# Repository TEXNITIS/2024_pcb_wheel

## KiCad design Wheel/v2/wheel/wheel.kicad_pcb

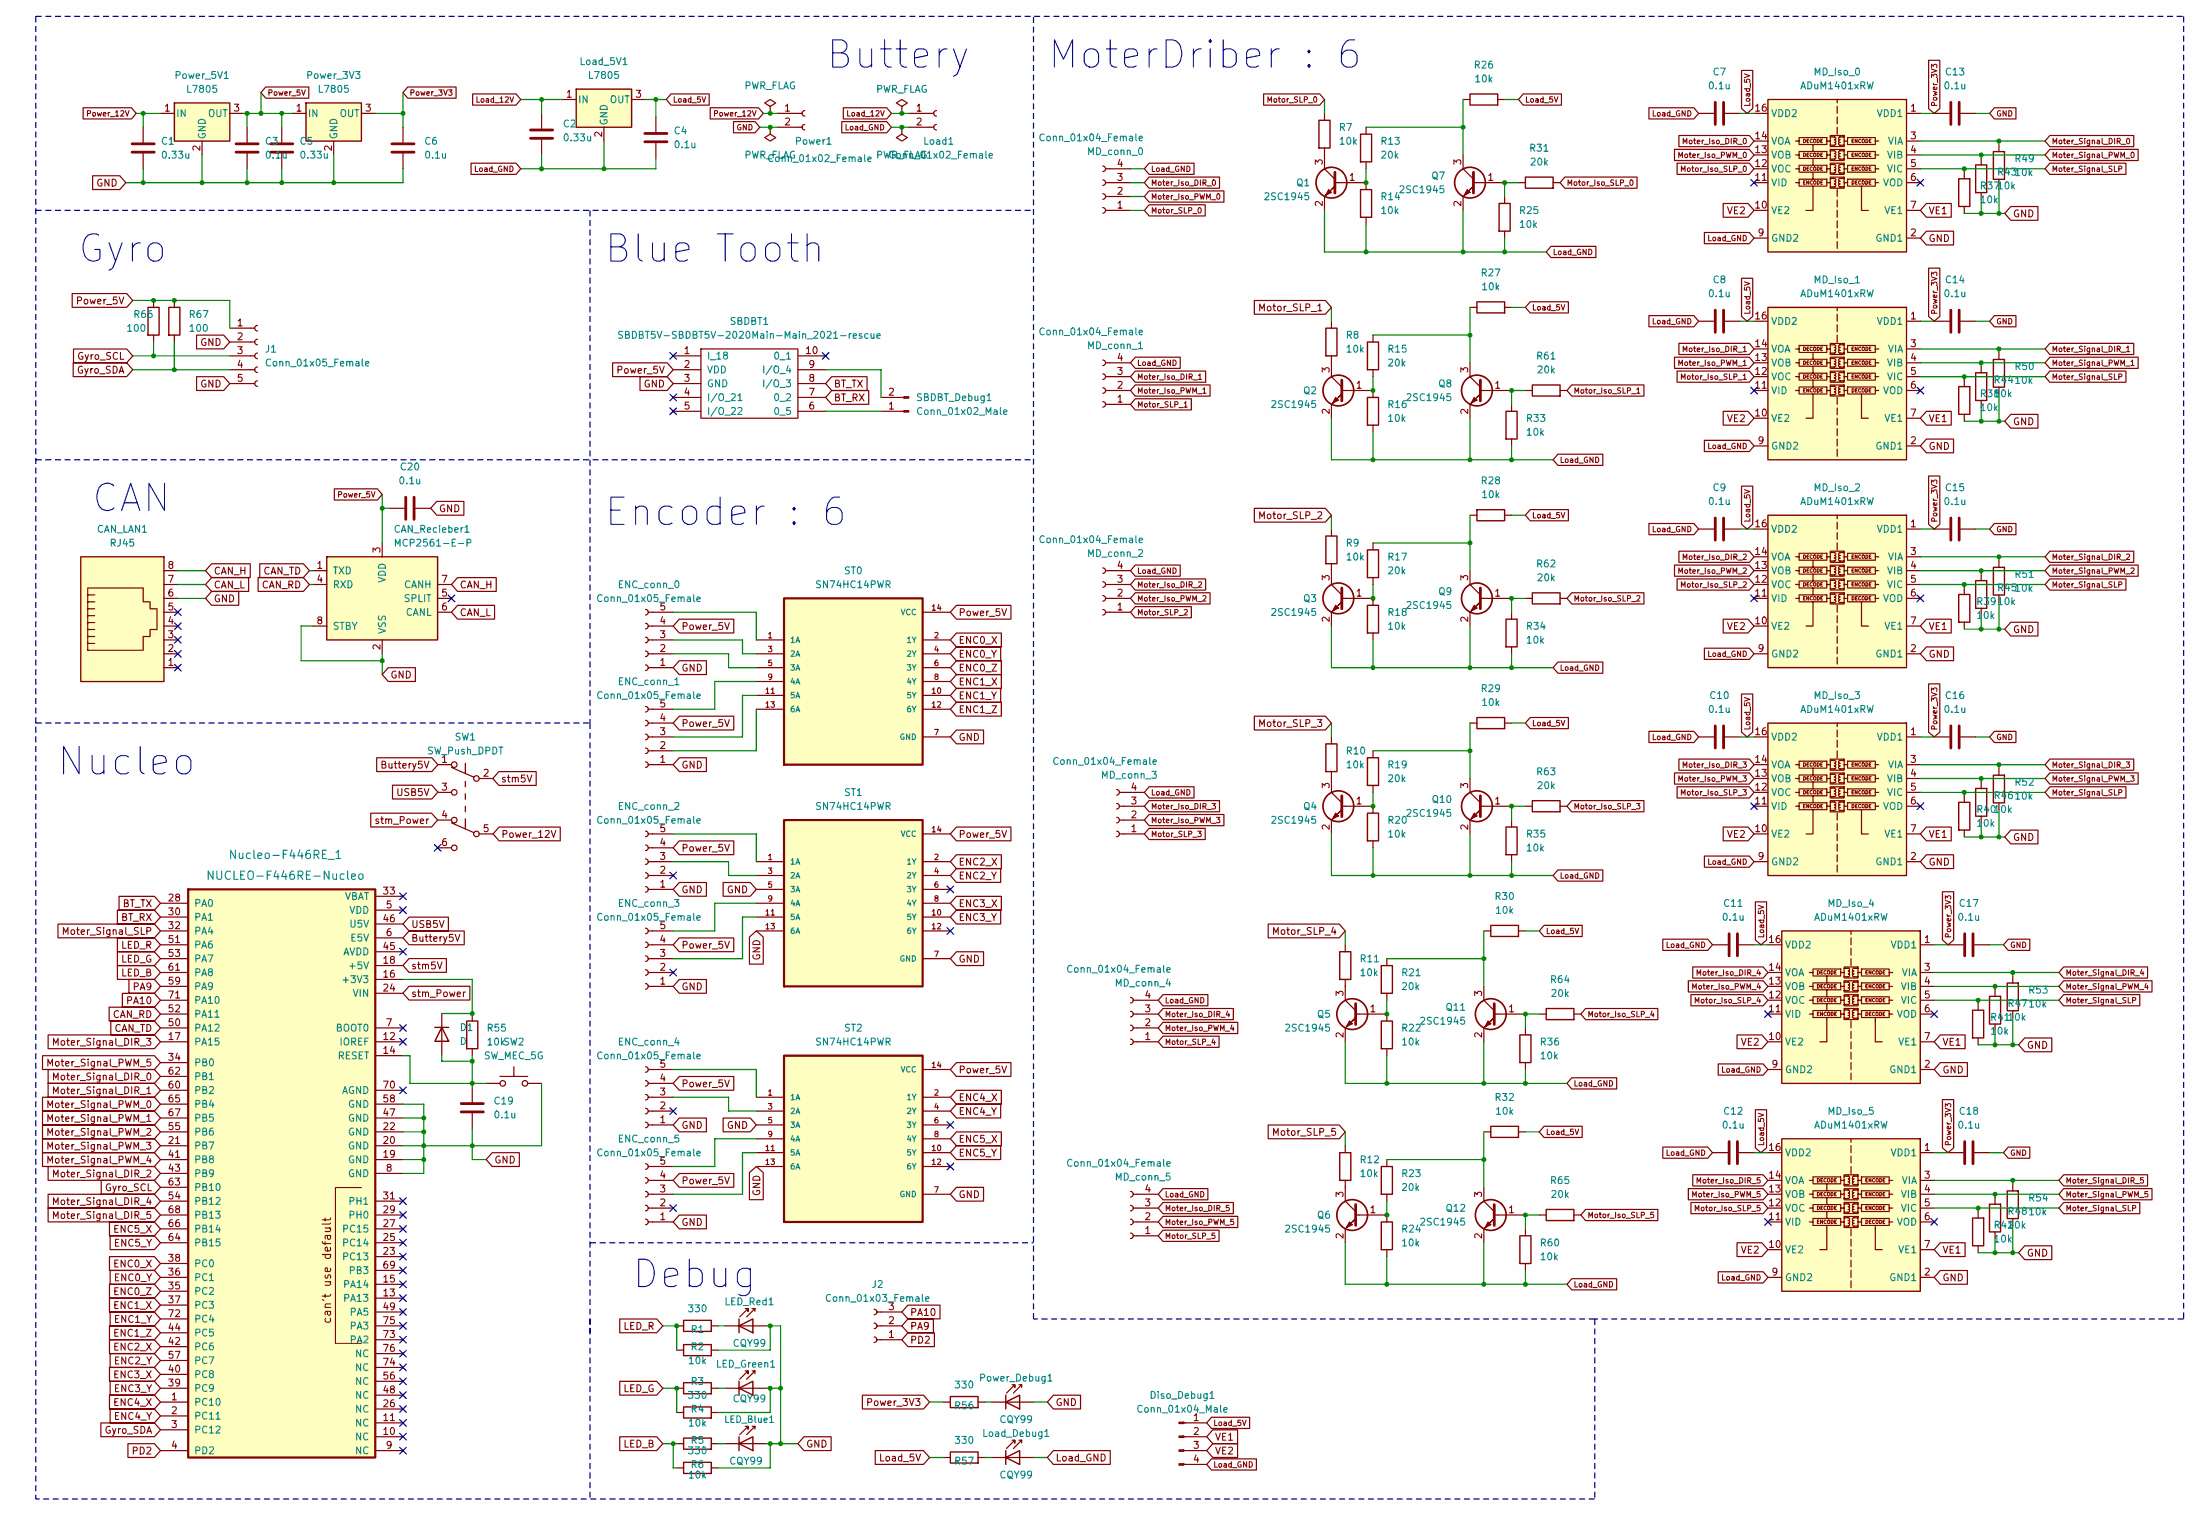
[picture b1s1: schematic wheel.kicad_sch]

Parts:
C1, C2, C5: 0.33u; C_0603_1608Metric_Pad1.08x0.95mm_HandSolder; LCSC C5139492
C3, C4, C6, C7, C8, C9, C10, C11, C12, C13, C14, C15, C16, C17, C18, C19: 0.1u; C_0603_1608Metric_Pad1.08x0.95mm_HandSolder; LCSC C14663
C20: 0.1u; C_0603_1608Metric_Pad1.08x0.95mm_HandSolder
CAN_LAN1: RJ45; RJ45_43860-0004
CAN_Recieber1: MCP2561-E-P; DIP-8_W7.62mm; LCSC C640341
D1: D; D_1206_3216Metric_Pad1.42x1.75mm_HandSolder
Diso_Debug1: Conn_01x04_Male; PinHeader_1x04_P2.54mm_Vertical
ENC_conn_0, ENC_conn_1, ENC_conn_2, ENC_conn_3, ENC_conn_4, ENC_conn_5: Conn_01x05_Female; JST_XH_S5B-XH-A_1x05_P2.50mm_Horizontal
J1: Conn_01x05_Female; PinSocket_1x05_P2.54mm_Vertical
J2: Conn_01x03_Female; PinHeader_1x03_P2.54mm_Vertical
LED_Blue1: CQY99; LED_PLCC-2_3.4x3.0mm_AK
LED_Green1: CQY99; LED_PLCC-2_3.4x3.0mm_AK
LED_Red1: CQY99; LED_PLCC-2_3.4x3.0mm_AK
Load1: Conn_01x02_Female; AMASS_XT60-F_1x02_P7.20mm_Vertical
Load_5V1: L7805; TO-252-3_TabPin2
Load_Debug1: CQY99; LED_PLCC-2_3.4x3.0mm_AK
MD_Iso_0, MD_Iso_1, MD_Iso_2, MD_Iso_3, MD_Iso_4, MD_Iso_5: ADuM1401xRW; SOIC-16W_7.5x10.3mm_P1.27mm; LCSC C91762
MD_conn_0, MD_conn_1, MD_conn_2, MD_conn_3, MD_conn_4, MD_conn_5: Conn_01x04_Female; JST_XH_S4B-XH-A_1x04_P2.50mm_Horizontal
Nucleo-F446RE_1: NUCLEO-F446RE-Nucleo; MODULE_NUCLEO-F446RE
Power1: Conn_01x02_Female; AMASS_XT60-F_1x02_P7.20mm_Vertical
Power_3V3, Power_5V1: L7805; TO-252-3_TabPin2
Power_Debug1: CQY99; LED_PLCC-2_3.4x3.0mm_AK
Q1, Q2, Q3, Q4, Q5, Q6, Q7, Q8, Q9, Q10, Q11, Q12: 2SC1945; SC-59_Handsoldering
R1, R3, R5, R56, R57: 330; R_0603_1608Metric_Pad0.98x0.95mm_HandSolder; LCSC C22978
R2, R4, R6, R7, R8, R9, R10, R11, R12, R14, R16, R18, R20, R22, R24, R25, R26, R27, R28, R29, R30, R32, R33, R34, R35, R36, R37, R38, R39, R40, R41, R42, R43, R44, R45, R46, R47, R48, R49, R50, R51, R52, R53, R54, R55, R60: 10k; R_0603_1608Metric_Pad0.98x0.95mm_HandSolder; LCSC C25804
R13, R15, R17, R19, R21, R23, R31, R61, R62, R63, R64, R65: 20k; R_0603_1608Metric_Pad0.98x0.95mm_HandSolder; LCSC C4184
R66, R67: 100; R_0603_1608Metric_Pad0.98x0.95mm_HandSolder
SBDBT1: SBDBT5V-SBDBT5V-2020Main-Main_2021-rescue; SBDBT5V
SBDBT_Debug1: Conn_01x02_Male; PinHeader_1x02_P2.54mm_Vertical
ST0, ST1, ST2: SN74HC14PWR; SOP65P640X120-14N; DigiKey_Part_Number 296-8234-2-ND
SW1: SW_Push_DPDT; SW_E-Switch_EG2219_DPDT_Angled
SW2: SW_MEC_5G; SW_Tactile_SPST_Angled_PTS645Vx39-2LFS

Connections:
BT_RX: Nucleo-F446RE_1.30 (PA1), SBDBT1.7 (0_2)
BT_TX: Nucleo-F446RE_1.28 (PA0), SBDBT1.8 (I/O_3)
Buttery5V: Nucleo-F446RE_1.6 (E5V), SW1.1 (A)
CAN_H: CAN_LAN1.8, CAN_Recieber1.7 (CANH)
CAN_L: CAN_LAN1.7, CAN_Recieber1.6 (CANL)
CAN_RD: CAN_Recieber1.4 (RXD), Nucleo-F446RE_1.52 (PA11)
CAN_TD: CAN_Recieber1.1 (TXD), Nucleo-F446RE_1.50 (PA12)
ENC0_X: Nucleo-F446RE_1.38 (PC0), ST0.2 (1Y)
ENC0_Y: Nucleo-F446RE_1.36 (PC1), ST0.4 (2Y)
ENC0_Z: Nucleo-F446RE_1.35 (PC2), ST0.6 (3Y)
ENC1_X: Nucleo-F446RE_1.37 (PC3), ST0.8 (4Y)
ENC1_Y: Nucleo-F446RE_1.72 (PC4), ST0.10 (5Y)
ENC1_Z: Nucleo-F446RE_1.44 (PC5), ST0.12 (6Y)
ENC2_X: Nucleo-F446RE_1.42 (PC6), ST1.2 (1Y)
ENC2_Y: Nucleo-F446RE_1.57 (PC7), ST1.4 (2Y)
ENC3_X: Nucleo-F446RE_1.40 (PC8), ST1.8 (4Y)
ENC3_Y: Nucleo-F446RE_1.39 (PC9), ST1.10 (5Y)
ENC4_X: Nucleo-F446RE_1.1 (PC10), ST2.2 (1Y)
ENC4_Y: Nucleo-F446RE_1.2 (PC11), ST2.4 (2Y)
ENC5_X: Nucleo-F446RE_1.66 (PB14), ST2.8 (4Y)
ENC5_Y: Nucleo-F446RE_1.64 (PB15), ST2.10 (5Y)
GND: C1.2, C3.2, C5.2, C6.2, C13.1, C14.1, C15.1, C16.1, C17.1, C18.1, C19.2, C20.1, CAN_LAN1.6, CAN_Recieber1.2 (VSS), CAN_Recieber1.8 (STBY), ENC_conn_0.1, ENC_conn_1.1, ENC_conn_2.1, ENC_conn_3.1, ENC_conn_4.1, ENC_conn_5.1, J1.2, J1.5, LED_Blue1.2 (A), LED_Green1.2 (A), LED_Red1.2 (A), MD_Iso_0.2 (GND1), MD_Iso_0.8 (GND1), MD_Iso_1.2 (GND1), MD_Iso_1.8 (GND1), MD_Iso_2.2 (GND1), MD_Iso_2.8 (GND1), MD_Iso_3.2 (GND1), MD_Iso_3.8 (GND1), MD_Iso_4.2 (GND1), MD_Iso_4.8 (GND1), MD_Iso_5.2 (GND1), MD_Iso_5.8 (GND1), Nucleo-F446RE_1.8 (GND), Nucleo-F446RE_1.19 (GND), Nucleo-F446RE_1.20 (GND), Nucleo-F446RE_1.22 (GND), Nucleo-F446RE_1.47 (GND), Nucleo-F446RE_1.58 (GND), Power1.2, Power_3V3.2 (GND), Power_5V1.2 (GND), Power_Debug1.2 (A), R2.2, R4.2, R6.2, R37.1, R38.1, R39.2, R40.2, R41.2, R42.1, R43.2, R44.1, R45.2, R46.1, R47.1, R48.1, R49.1, R50.1, R51.1, R52.1, R53.1, R54.1, SBDBT1.3 (GND), ST0.7 (GND), ST1.5 (3A), ST1.7 (GND), ST1.13 (6A), ST2.5 (3A), ST2.7 (GND), ST2.13 (6A), SW2.3 (B), SW2.4 (B)
Gyro_SCL: J1.3, Nucleo-F446RE_1.63 (PB10), R66.2
Gyro_SDA: J1.4, Nucleo-F446RE_1.3 (PC12), R67.2
LED_B: Nucleo-F446RE_1.61 (PA8), R5.1, R6.1
LED_G: Nucleo-F446RE_1.53 (PA7), R3.1, R4.1
LED_R: Nucleo-F446RE_1.51 (PA6), R1.1, R2.1
Load_5V: C4.1, C7.2, C8.2, C9.2, C10.1, C11.1, C12.1, Diso_Debug1.1, Load_5V1.3 (OUT), MD_Iso_0.16 (VDD2), MD_Iso_1.16 (VDD2), MD_Iso_2.16 (VDD2), MD_Iso_3.16 (VDD2), MD_Iso_4.16 (VDD2), MD_Iso_5.16 (VDD2), R26.2, R27.2, R28.1, R29.2, R30.2, R32.2, R57.1
Load_12V: C2.1, Load1.1, Load_5V1.1 (IN)
Load_GND: C2.2, C4.2, C7.1, C8.1, C9.1, C10.2, C11.2, C12.2, Diso_Debug1.4, Load1.2, Load_5V1.2 (GND), Load_Debug1.2 (A), MD_Iso_0.9 (GND2), MD_Iso_0.15 (GND2), MD_Iso_1.9 (GND2), MD_Iso_1.15 (GND2), MD_Iso_2.9 (GND2), MD_Iso_2.15 (GND2), MD_Iso_3.9 (GND2), MD_Iso_3.15 (GND2), MD_Iso_4.9 (GND2), MD_Iso_4.15 (GND2), MD_Iso_5.9 (GND2), MD_Iso_5.15 (GND2), MD_conn_0.4, MD_conn_1.4, MD_conn_2.4, MD_conn_3.4, MD_conn_4.4, MD_conn_5.4, Q1.2 (E), Q2.2 (E), Q3.2 (E), Q4.2 (E), Q5.2 (E), Q6.2 (E), Q7.2 (E), Q8.2 (E), Q9.2 (E), Q10.2 (E), Q11.2 (E), Q12.2 (E), R14.2, R16.2, R18.2, R20.2, R22.2, R24.2, R25.2, R33.2, R34.2, R35.2, R36.2, R60.2
Moter_Iso_DIR_0: MD_Iso_0.14 (VOA), MD_conn_0.3
Moter_Iso_DIR_1: MD_Iso_1.14 (VOA), MD_conn_1.3
Moter_Iso_DIR_2: MD_Iso_2.14 (VOA), MD_conn_2.3
Moter_Iso_DIR_3: MD_Iso_3.14 (VOA), MD_conn_3.3
Moter_Iso_DIR_4: MD_Iso_4.14 (VOA), MD_conn_4.3
Moter_Iso_DIR_5: MD_Iso_5.14 (VOA), MD_conn_5.3
Moter_Iso_PWM_0: MD_Iso_0.13 (VOB), MD_conn_0.2
Moter_Iso_PWM_1: MD_Iso_1.13 (VOB), MD_conn_1.2
Moter_Iso_PWM_2: MD_Iso_2.13 (VOB), MD_conn_2.2
Moter_Iso_PWM_3: MD_Iso_3.13 (VOB), MD_conn_3.2
Moter_Iso_PWM_4: MD_Iso_4.13 (VOB), MD_conn_4.2
Moter_Iso_PWM_5: MD_Iso_5.13 (VOB), MD_conn_5.2
Moter_Signal_DIR_0: MD_Iso_0.3 (VIA), Nucleo-F446RE_1.62 (PB1), R49.2
Moter_Signal_DIR_1: MD_Iso_1.3 (VIA), Nucleo-F446RE_1.60 (PB2), R50.2
Moter_Signal_DIR_2: MD_Iso_2.3 (VIA), Nucleo-F446RE_1.43 (PB9), R51.2
Moter_Signal_DIR_3: MD_Iso_3.3 (VIA), Nucleo-F446RE_1.17 (PA15), R52.2
Moter_Signal_DIR_4: MD_Iso_4.3 (VIA), Nucleo-F446RE_1.54 (PB12), R53.2
Moter_Signal_DIR_5: MD_Iso_5.3 (VIA), Nucleo-F446RE_1.68 (PB13), R54.2
Moter_Signal_PWM_0: MD_Iso_0.4 (VIB), Nucleo-F446RE_1.65 (PB4), R43.1
Moter_Signal_PWM_1: MD_Iso_1.4 (VIB), Nucleo-F446RE_1.67 (PB5), R44.2
Moter_Signal_PWM_2: MD_Iso_2.4 (VIB), Nucleo-F446RE_1.55 (PB6), R45.1
Moter_Signal_PWM_3: MD_Iso_3.4 (VIB), Nucleo-F446RE_1.21 (PB7), R46.2
Moter_Signal_PWM_4: MD_Iso_4.4 (VIB), Nucleo-F446RE_1.41 (PB8), R47.2
Moter_Signal_PWM_5: MD_Iso_5.4 (VIB), Nucleo-F446RE_1.34 (PB0), R48.2
Moter_Signal_SLP: MD_Iso_0.5 (VIC), MD_Iso_1.5 (VIC), MD_Iso_2.5 (VIC), MD_Iso_3.5 (VIC), MD_Iso_4.5 (VIC), MD_Iso_5.5 (VIC), Nucleo-F446RE_1.32 (PA4), R37.2, R38.2, R39.1, R40.1, R41.1, R42.2
Motor_Iso_SLP_0: MD_Iso_0.12 (VOC), R31.2
Motor_Iso_SLP_1: MD_Iso_1.12 (VOC), R61.2
Motor_Iso_SLP_2: MD_Iso_2.12 (VOC), R62.2
Motor_Iso_SLP_3: MD_Iso_3.12 (VOC), R63.2
Motor_Iso_SLP_4: MD_Iso_4.12 (VOC), R64.2
Motor_Iso_SLP_5: MD_Iso_5.12 (VOC), R65.2
Motor_SLP_0: MD_conn_0.1, R7.1
Motor_SLP_1: MD_conn_1.1, R8.1
Motor_SLP_2: MD_conn_2.1, R9.1
Motor_SLP_3: MD_conn_3.1, R10.1
Motor_SLP_4: MD_conn_4.1, R11.1
Motor_SLP_5: MD_conn_5.1, R12.1
unnamed: C19.1, D1.2 (A), Nucleo-F446RE_1.14 (RESET), R55.2, SW2.1 (A), SW2.2 (A)
unnamed: D1.1 (K), Nucleo-F446RE_1.16 (+3V3), R55.1
unnamed: ENC_conn_0.2, ST0.5 (3A)
unnamed: ENC_conn_0.3, ST0.3 (2A)
unnamed: ENC_conn_0.5, ST0.1 (1A)
unnamed: ENC_conn_1.2, ST0.13 (6A)
unnamed: ENC_conn_1.3, ST0.11 (5A)
unnamed: ENC_conn_1.5, ST0.9 (4A)
unnamed: ENC_conn_2.3, ST1.3 (2A)
unnamed: ENC_conn_2.5, ST1.1 (1A)
unnamed: ENC_conn_3.3, ST1.11 (5A)
unnamed: ENC_conn_3.5, ST1.9 (4A)
unnamed: ENC_conn_4.3, ST2.3 (2A)
unnamed: ENC_conn_4.5, ST2.1 (1A)
unnamed: ENC_conn_5.3, ST2.11 (5A)
unnamed: ENC_conn_5.5, ST2.9 (4A)
unnamed: LED_Blue1.1 (K), R5.2
unnamed: LED_Green1.1 (K), R3.2
unnamed: LED_Red1.1 (K), R1.2
unnamed: Load_Debug1.1 (K), R57.2
unnamed: Power_Debug1.1 (K), R56.2
unnamed: Q1.1 (B), R13.2, R14.1
unnamed: Q1.3 (C), R7.2
unnamed: Q2.1 (B), R15.2, R16.1
unnamed: Q2.3 (C), R8.2
unnamed: Q3.1 (B), R17.2, R18.1
unnamed: Q3.3 (C), R9.2
unnamed: Q4.1 (B), R19.2, R20.1
unnamed: Q4.3 (C), R10.2
unnamed: Q5.1 (B), R21.2, R22.1
unnamed: Q5.3 (C), R11.2
unnamed: Q6.1 (B), R23.2, R24.1
unnamed: Q6.3 (C), R12.2
unnamed: Q7.1 (B), R25.1, R31.1
unnamed: Q7.3 (C), R13.1, R26.1
unnamed: Q8.1 (B), R33.1, R61.1
unnamed: Q8.3 (C), R15.1, R27.1
unnamed: Q9.1 (B), R34.1, R62.1
unnamed: Q9.3 (C), R17.1, R28.2
unnamed: Q10.1 (B), R35.1, R63.1
unnamed: Q10.3 (C), R19.1, R29.1
unnamed: Q11.1 (B), R36.1, R64.1
unnamed: Q11.3 (C), R21.1, R30.1
unnamed: Q12.1 (B), R60.1, R65.1
unnamed: Q12.3 (C), R23.1, R32.1
unnamed: SBDBT1.6 (0_5), SBDBT_Debug1.1
unnamed: SBDBT1.9 (I/O_4), SBDBT_Debug1.2
PA9: J2.2, Nucleo-F446RE_1.59 (PA9)
PA10: J2.3, Nucleo-F446RE_1.71 (PA10)
PD2: J2.1, Nucleo-F446RE_1.4 (PD2)
Power_3V3: C6.1, C13.2, C14.2, C15.2, C16.2, C17.2, C18.2, MD_Iso_0.1 (VDD1), MD_Iso_1.1 (VDD1), MD_Iso_2.1 (VDD1), MD_Iso_3.1 (VDD1), MD_Iso_4.1 (VDD1), MD_Iso_5.1 (VDD1), Power_3V3.3 (OUT), R56.1
Power_5V: C3.1, C5.1, C20.2, CAN_Recieber1.3 (VDD), ENC_conn_0.4, ENC_conn_1.4, ENC_conn_2.4, ENC_conn_3.4, ENC_conn_4.4, ENC_conn_5.4, J1.1, Power_3V3.1 (IN), Power_5V1.3 (OUT), R66.1, R67.1, SBDBT1.2 (VDD), ST0.14 (VCC), ST1.14 (VCC), ST2.14 (VCC)
Power_12V: C1.1, Power1.1, Power_5V1.1 (IN), SW1.5 (B)
USB5V: Nucleo-F446RE_1.46 (U5V), SW1.3 (C)
VE1: Diso_Debug1.2, MD_Iso_0.7 (VE1), MD_Iso_1.7 (VE1), MD_Iso_2.7 (VE1), MD_Iso_3.7 (VE1), MD_Iso_4.7 (VE1), MD_Iso_5.7 (VE1)
VE2: Diso_Debug1.3, MD_Iso_0.10 (VE2), MD_Iso_1.10 (VE2), MD_Iso_2.10 (VE2), MD_Iso_3.10 (VE2), MD_Iso_4.10 (VE2), MD_Iso_5.10 (VE2)
stm5V: Nucleo-F446RE_1.18 (+5V), SW1.2 (B)
stm_Power: Nucleo-F446RE_1.24 (VIN), SW1.4 (A)

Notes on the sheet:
CAN
Nucleo
Blue Tooth
Buttery
Gyro
Encoder : 6
Debug
MoterDriber : 6

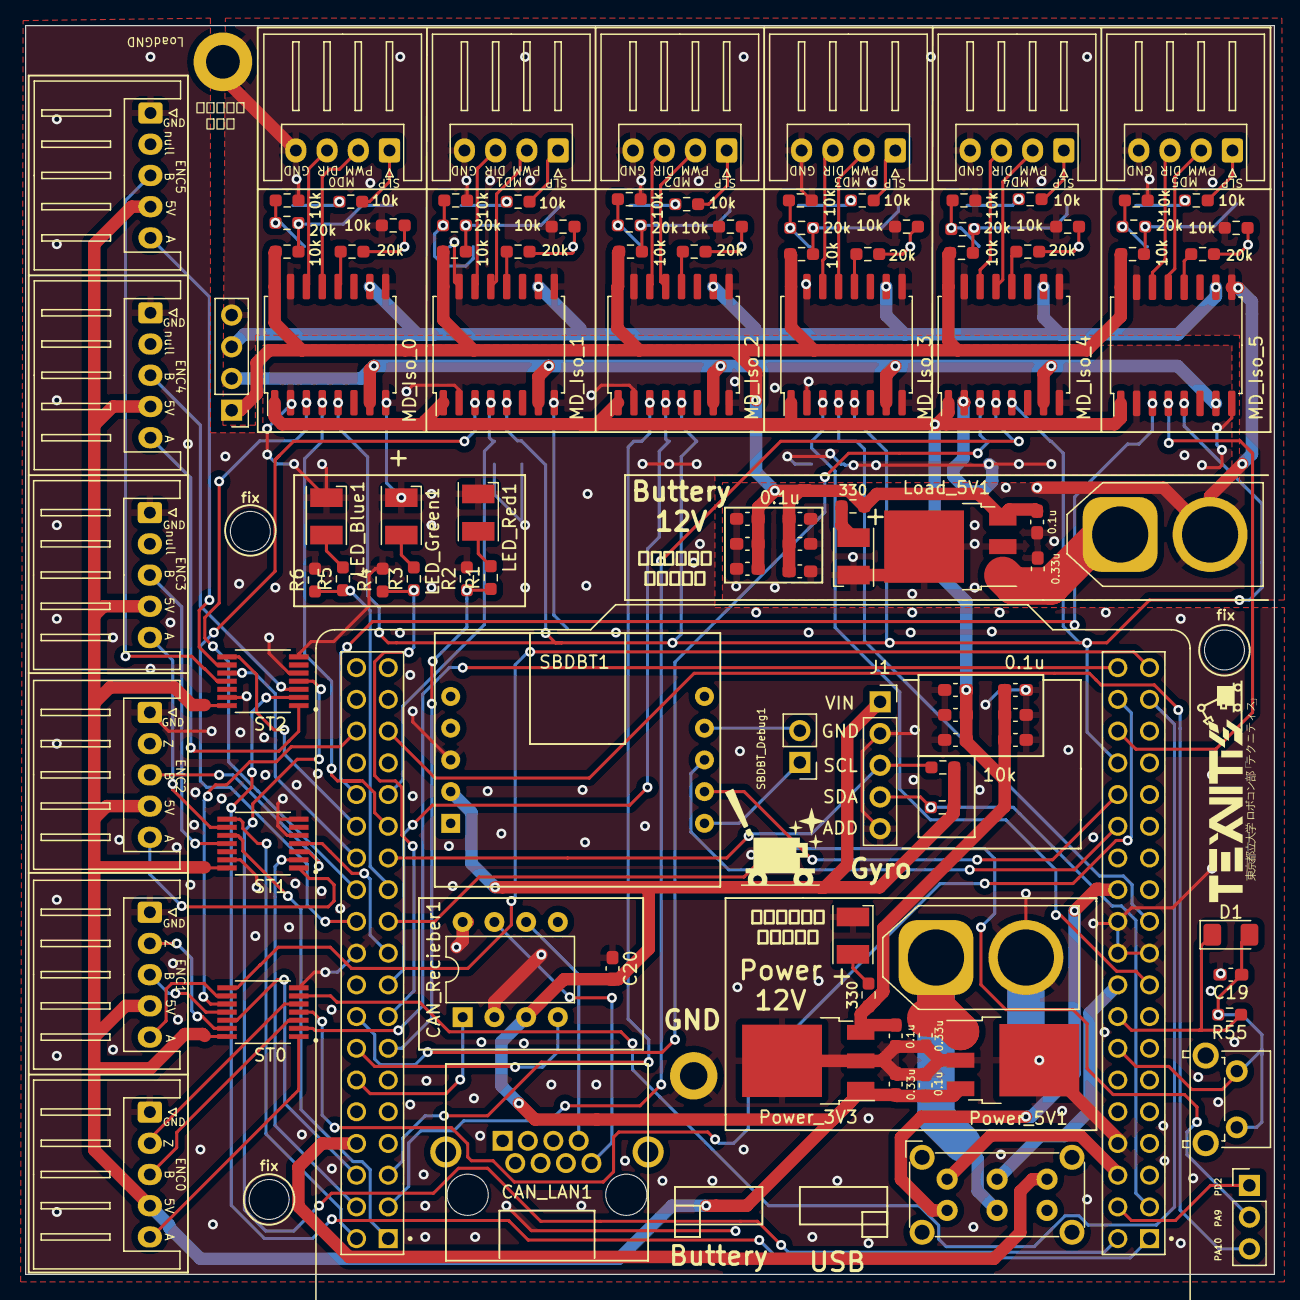
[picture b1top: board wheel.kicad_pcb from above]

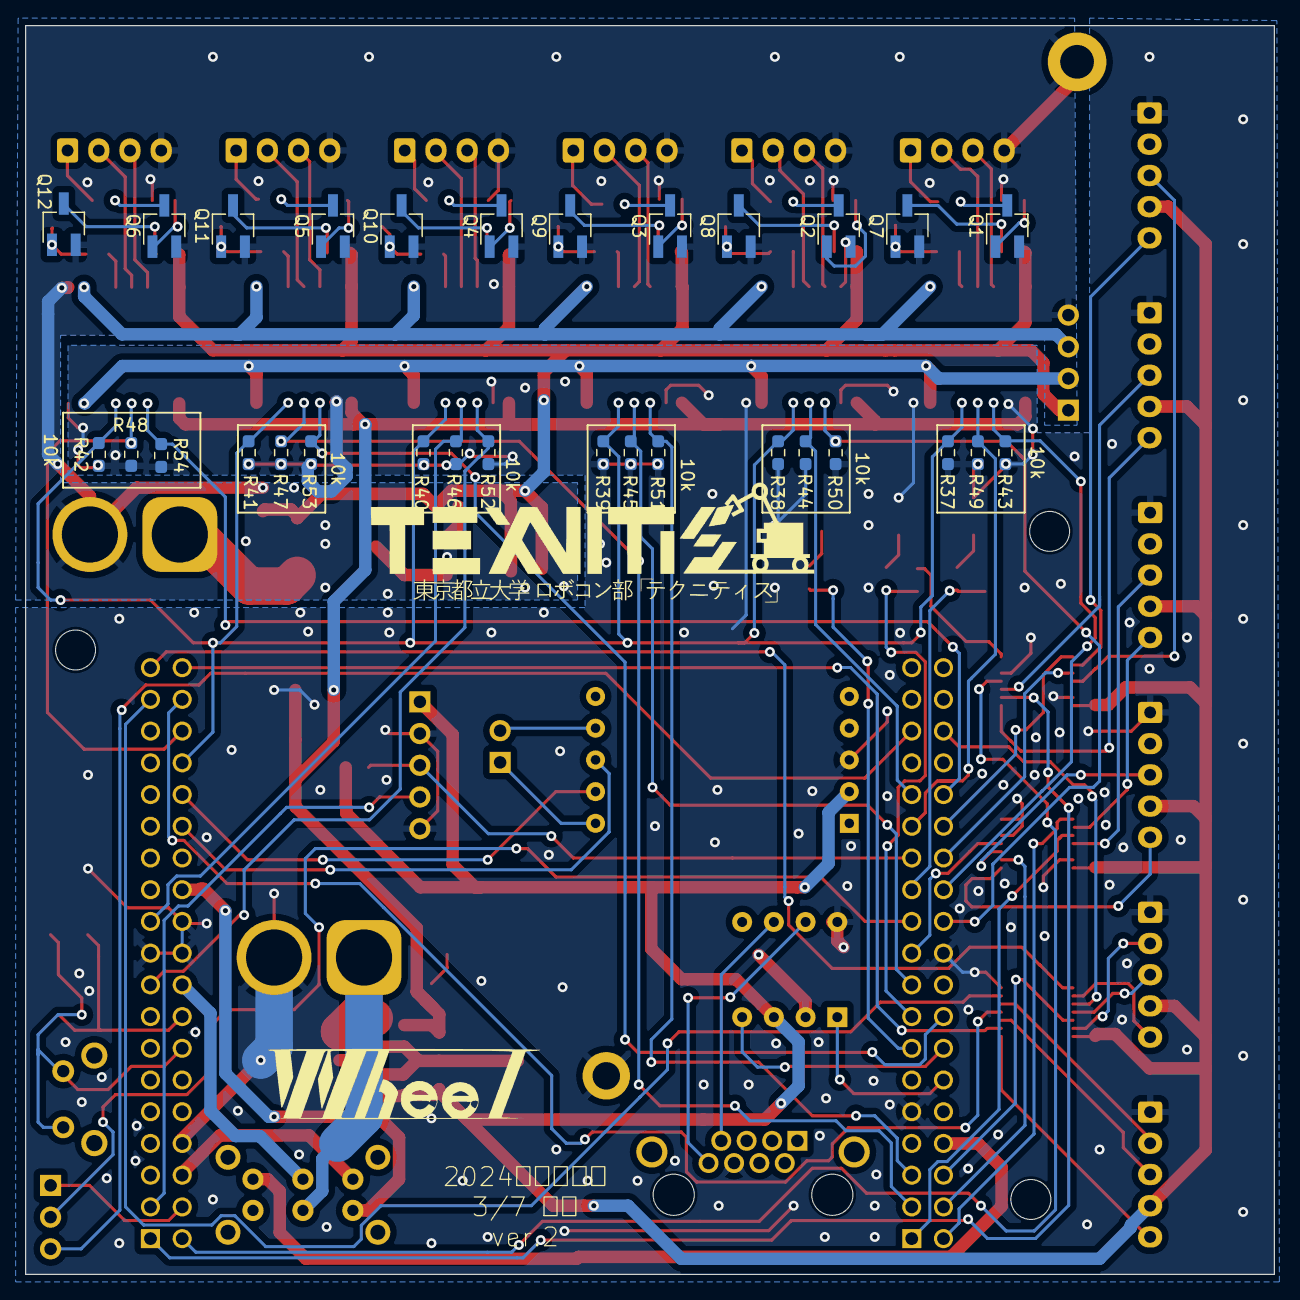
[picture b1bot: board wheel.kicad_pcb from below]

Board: 2 copper layers, 100.0 x 100.0 mm, 139 parts (30 on the bottom side), 125 nets.

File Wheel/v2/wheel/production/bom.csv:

Designator,Footprint,Quantity,Value,LCSC Part #
"C1, C2, C5",0603,3,0.33u,C5139492
"C10, C11, C12, C13, C14, C15, C16, C17, C18, C19, C3, C4, C6, C7, C8, C9",0603,16,0.1u,C14663
C20,0603,1,0.1u,
CAN_LAN1,RJ45_43860-0004,1,RJ45,
CAN_Recieber1,DIP-8_W7.62mm,1,MCP2561-E-P,C640341
D1,1206,1,D,
Diso_Debug1,PinHeader_1x04_P2.54mm_Vertical,1,Conn_01x04_Male,
"ENC_conn_0, ENC_conn_1, ENC_conn_2, ENC_conn_3, ENC_conn_4, ENC_conn_5",JST_XH_S5B-XH-A_1x05_P2.50mm_Horizontal,6,Conn_01x05_Female,
J1,PinSocket_1x05_P2.54mm_Vertical,1,Conn_01x05_Female,
J2,PinHeader_1x03_P2.54mm_Vertical,1,Conn_01x03_Female,
"LED_Blue1, LED_Green1, LED_Red1, Load_Debug1, Power_Debug1",LED_PLCC-2_3.4x3.0mm_AK,5,CQY99,
"Load1, Power1",AMASS_XT60-F_1x02_P7.20mm_Vertical,2,Conn_01x02_Female,
"Load_5V1, Power_3V3, Power_5V1",TO-252-3_TabPin2,3,L7805,
"MD_Iso_0, MD_Iso_1, MD_Iso_2, MD_Iso_3, MD_Iso_4, MD_Iso_5",SOIC-16W_7.5x10.3mm_P1.27mm,6,ADuM1401xRW,C91762
"MD_conn_0, MD_conn_1, MD_conn_2, MD_conn_3, MD_conn_4, MD_conn_5",JST_XH_S4B-XH-A_1x04_P2.50mm_Horizontal,6,Conn_01x04_Female,
Nucleo-F446RE_1,MODULE_NUCLEO-F446RE,1,NUCLEO-F446RE-Nucleo,
"Q1, Q10, Q11, Q12, Q2, Q3, Q4, Q5, Q6, Q7, Q8, Q9",SC-59_Handsoldering,12,2SC1945,
"R1, R3, R5, R56, R57",0603,5,330,C22978
"R10, R11, R12, R14, R16, R18, R2, R20, R22, R24, R25, R26, R27, R28, R29, R30, R32, R33, R34, R35, R36, R37, R38, R39, R4, R40, R41, R42, R43, R44, R45, R46, R47, R48, R49, R50, R51, R52, R53, R54, R55, R6, R60, R7, R8, R9",0603,46,10k,C25804
"R13, R15, R17, R19, R21, R23, R31, R61, R62, R63, R64, R65",0603,12,20k,C4184
"R66, R67",0603,2,100,
SBDBT1,SBDBT5V,1,SBDBT5V-SBDBT5V-2020Main-Main_2021-rescue,
SBDBT_Debug1,PinHeader_1x02_P2.54mm_Vertical,1,Conn_01x02_Male,
"ST0, ST1, ST2",SOP65P640X120-14N,3,SN74HC14PWR,C6821 
SW1,SW_E-Switch_EG2219_DPDT_Angled,1,SW_Push_DPDT,
SW2,SW_Tactile_SPST_Angled_PTS645Vx39-2LFS,1,SW_MEC_5G,

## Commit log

2024-04-16 commit v3 data
